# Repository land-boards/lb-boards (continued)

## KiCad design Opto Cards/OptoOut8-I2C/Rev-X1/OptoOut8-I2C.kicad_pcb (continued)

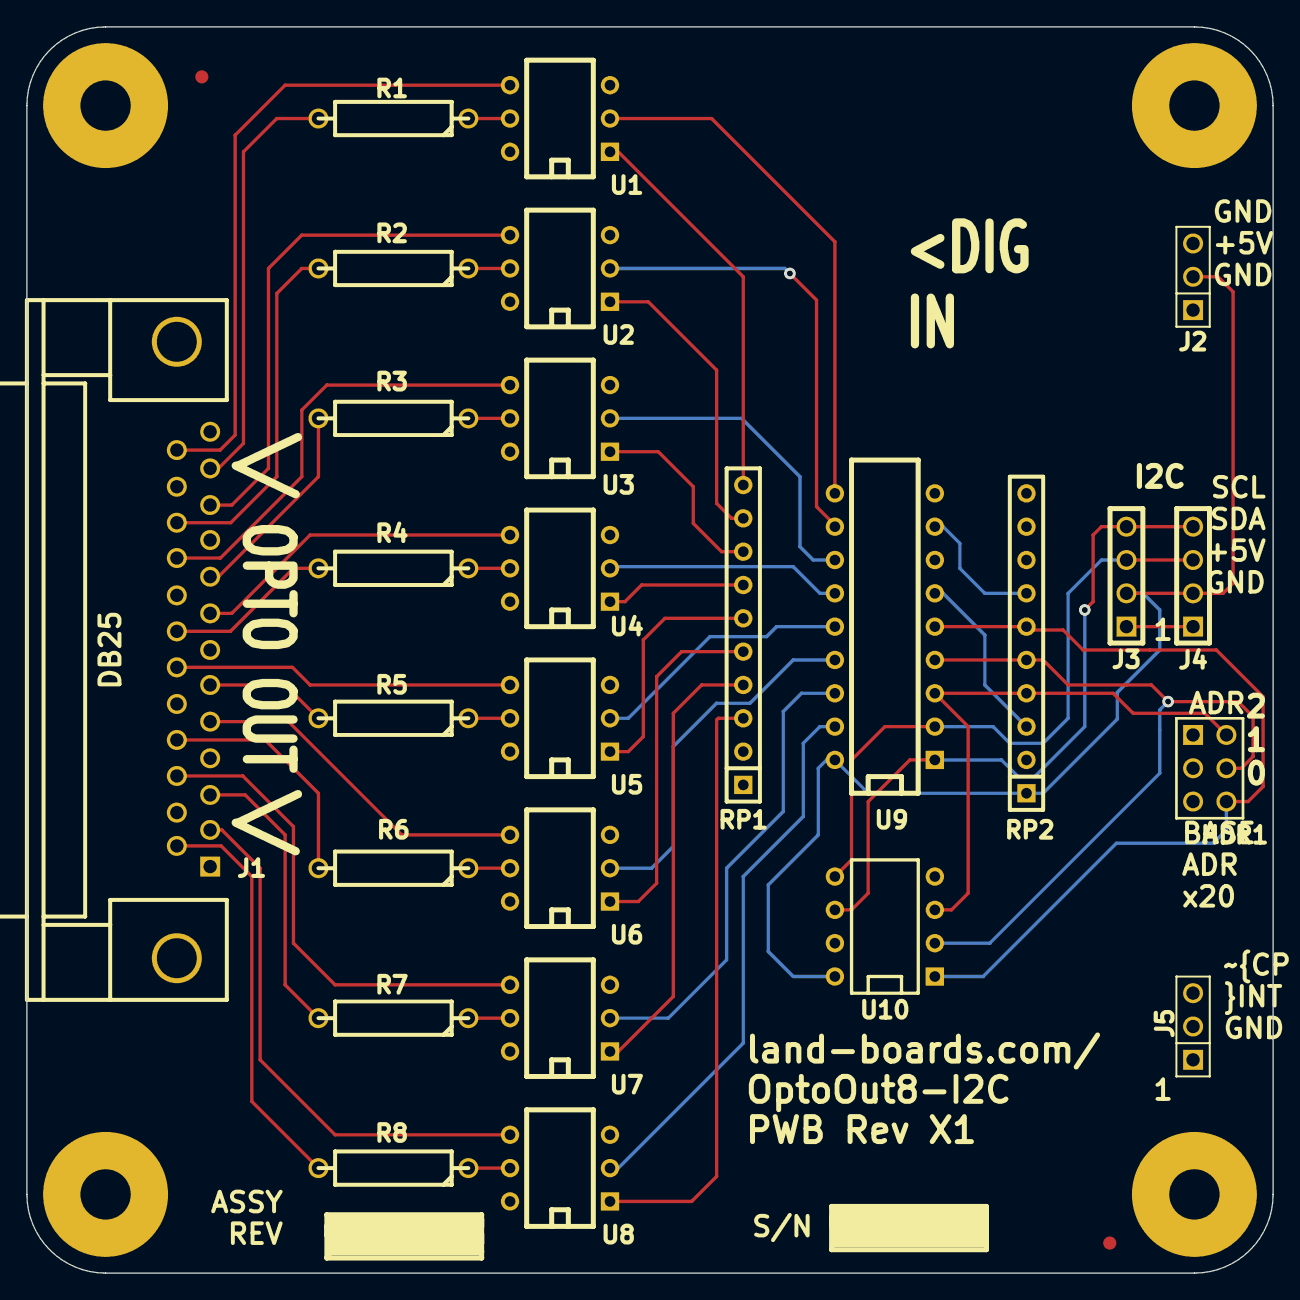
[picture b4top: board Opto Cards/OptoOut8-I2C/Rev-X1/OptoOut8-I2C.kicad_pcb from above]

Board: 2 copper layers, 95.0 x 95.0 mm, 34 parts (0 on the bottom side), 49 nets.
